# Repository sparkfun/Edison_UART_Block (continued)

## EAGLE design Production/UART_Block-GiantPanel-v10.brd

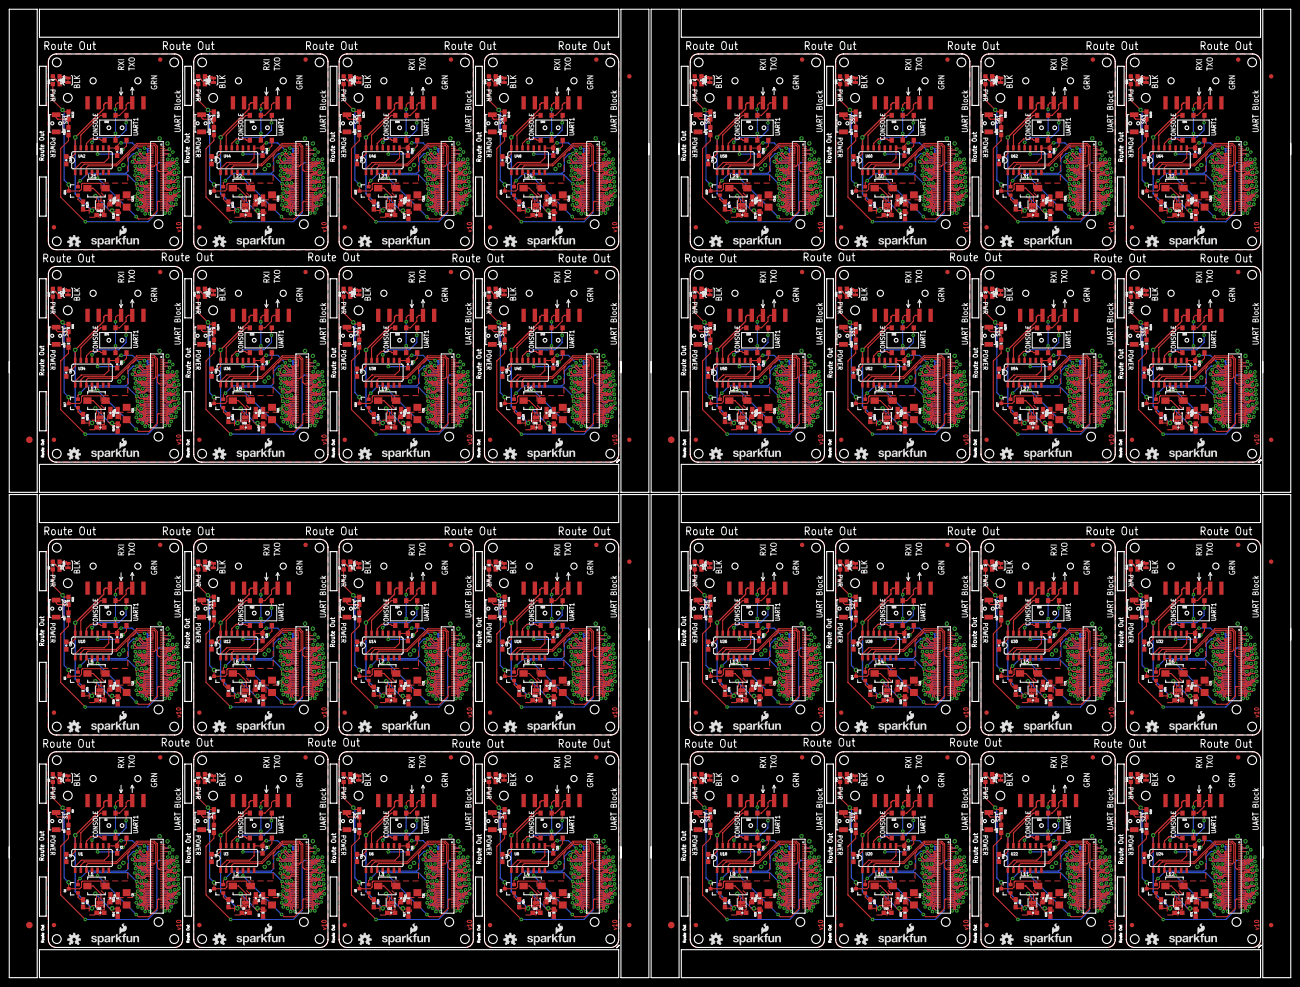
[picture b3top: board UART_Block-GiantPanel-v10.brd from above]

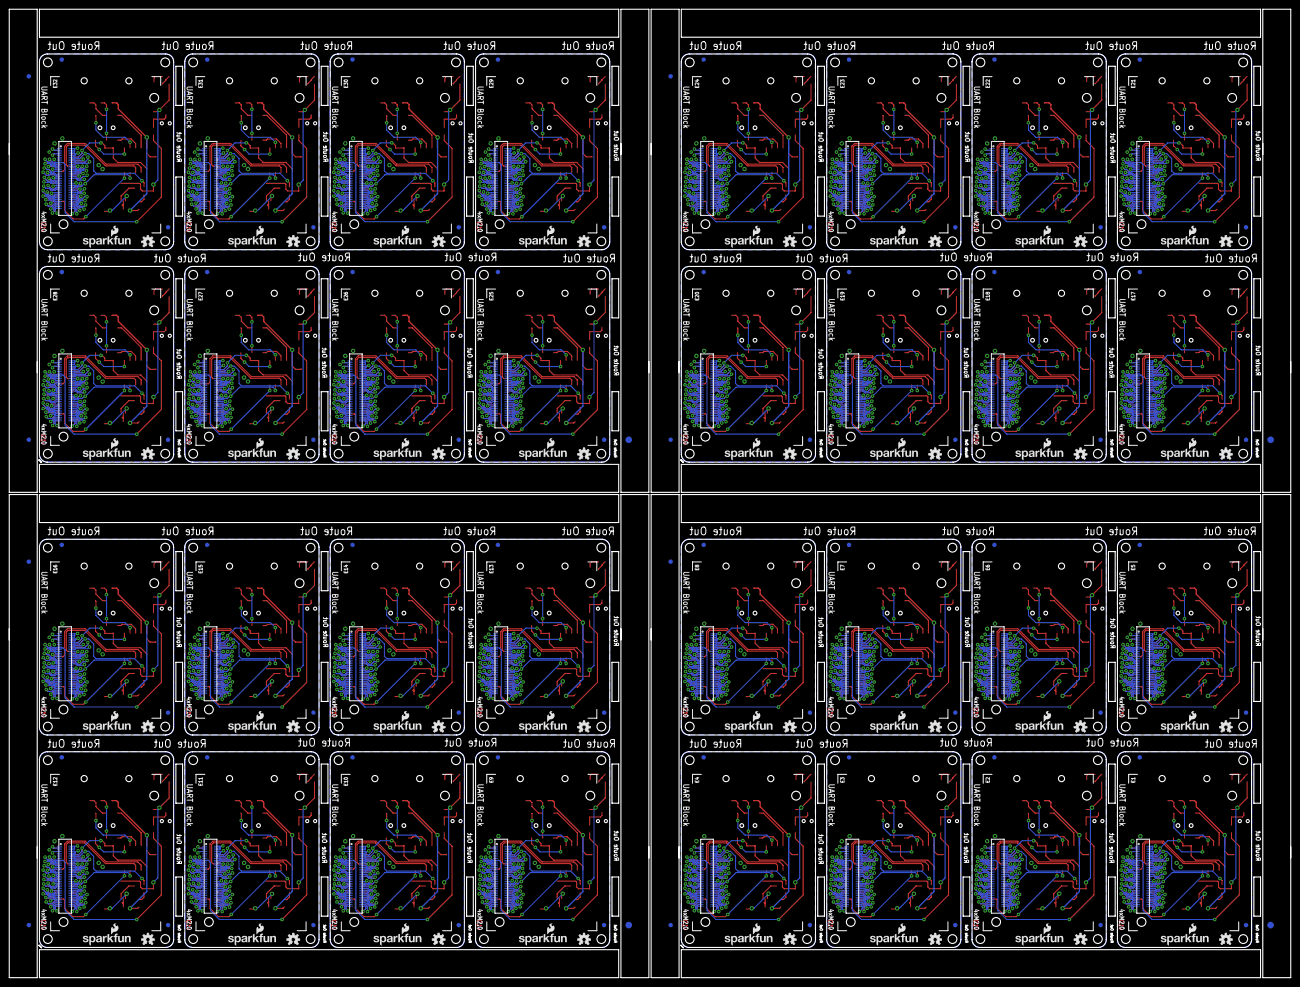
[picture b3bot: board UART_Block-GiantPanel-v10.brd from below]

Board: 2 copper layers, 291.1 x 220.0 mm, 984 parts (204 on the bottom side), 2272 nets.

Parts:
C1, C2, C6, C7, C14, C15, C19, C20, C24, C25, C29, C30, C34, C35, C39, C40, C44, C45, C49, C50, C54, C55, C59, C60, C64, C65, C69, C70, C74, C75, C79, C80, C84, C85, C89, C90, C94, C95, C99, C100, C104, C105, C109, C110, C114, C115, C119, C120, C124, C125, C129, C130, C134, C135, C139, C140, C144, C145, C149, C150, C154, C155, C159, C160: 0.1uF; 0603-CAP
C3, C8, C11, C16, C21, C26, C31, C36, C41, C46, C51, C56, C61, C66, C71, C76, C81, C86, C91, C96, C101, C106, C111, C116, C121, C126, C131, C136, C141, C146, C151, C156: 10uF; 1206
C4, C9, C12, C17, C22, C27, C32, C37, C42, C47, C52, C57, C62, C67, C72, C77, C82, C87, C92, C97, C102, C107, C112, C117, C122, C127, C132, C137, C142, C147, C152, C157: 47pF; 0603-CAP
C5, C10, C13, C18, C23, C28, C33, C38, C43, C48, C53, C58, C63, C68, C73, C78, C83, C88, C93, C98, C103, C108, C113, C118, C123, C128, C133, C138, C143, C148, C153, C158: 4.7uF; 0603-CAP
D1, D2, D3, D4, D5, D6, D7, D8, D9, D10, D11, D12, D13, D14, D15, D16, D17, D18, D19, D20, D21, D22, D23, D24, D25, D26, D27, D28, D29, D30, D31, D32: BLUE; LED-0603
E1, E2, E3, E4, E5, E6, E7, E8, E9, E10, E11, E12, E13, E14, E15, E16, E17, E18, E19, E20, E21, E22, E23, E24, E25, E26, E27, E28, E29, E30, E31, E32: EDISON_CONNECTOR_FULLMOUNTING_HOLES; EDISON_DAUGHTER
E$1, E$2, E$9, E$10, E$15, E$16, E$21, E$22: FIDUCIAL-1.5X3
E$3, E$4, E$5, E$6, E$7, E$8, E$11, E$12, E$13, E$14, E$17, E$18, E$19, E$20, E$23, E$24: FIDUCIAL-1X2
FID1, FID2, FID3, FID4, FID5, FID6, FID7, FID8, FID9, FID10, FID11, FID12, FID13, FID14, FID15, FID16, FID17, FID18, FID19, FID20, FID21, FID22, FID23, FID24, FID25, FID26, FID27, FID28, FID29, FID30, FID31, FID32, FID33, FID34, FID35, FID36, FID37, FID38, FID39, FID40, FID41, FID42, FID43, FID44, FID45, FID46, FID47, FID48, FID49, FID50, FID51, FID52, FID53, FID54, FID55, FID56, FID57, FID58, FID59, FID60, FID61, FID62, FID63, FID64, FID65, FID66, FID67, FID68, FID69, FID70, FID71, FID72, FID73, FID74, FID75, FID76, FID77, FID78, FID79, FID80, FID81, FID82, FID83, FID84, FID85, FID86, FID87, FID88, FID89, FID90, FID91, FID92, FID93, FID94, FID95, FID96, FID97, FID98, FID99, FID100, FID101, FID102, FID103, FID104, FID105, FID106, FID107, FID108, FID109, FID110, FID111, FID112, FID113, FID114, FID115, FID116, FID117, FID118, FID119, FID120, FID121, FID122, FID123, FID124, FID125, FID126, FID127, FID128: FIDUCIAL1X2; FIDUCIAL-1X2
JP1, JP2, JP3, JP4, JP5, JP6, JP7, JP8, JP9, JP10, JP11, JP12, JP13, JP14, JP15, JP16, JP17, JP18, JP19, JP20, JP21, JP22, JP23, JP24, JP25, JP26, JP27, JP28, JP29, JP30, JP31, JP32: 1X06-SMD
L1, L2, L3, L4, L5, L6, L7, L8, L9, L10, L11, L12, L13, L14, L15, L16, L17, L18, L19, L20, L21, L22, L23, L24, L25, L26, L27, L28, L29, L30, L31, L32: INDUCTOR-SRP4020
LOGO1, LOGO3, LOGO6, LOGO7, LOGO10, LOGO11, LOGO14, LOGO15, LOGO18, LOGO19, LOGO22, LOGO23, LOGO26, LOGO27, LOGO30, LOGO31, LOGO34, LOGO35, LOGO38, LOGO39, LOGO42, LOGO43, LOGO46, LOGO47, LOGO50, LOGO51, LOGO54, LOGO55, LOGO58, LOGO59, LOGO62, LOGO63, LOGO66, LOGO67, LOGO70, LOGO71, LOGO74, LOGO75, LOGO78, LOGO79, LOGO82, LOGO83, LOGO86, LOGO87, LOGO90, LOGO91, LOGO94, LOGO95, LOGO98, LOGO99, LOGO102, LOGO103, LOGO106, LOGO107, LOGO110, LOGO111, LOGO114, LOGO115, LOGO118, LOGO119, LOGO122, LOGO123, LOGO126, LOGO127: SFE_LOGO_NAME_FLAME.1_INCH; SFE_LOGO_NAME_FLAME_.1
LOGO2, LOGO4, LOGO5, LOGO8, LOGO9, LOGO12, LOGO13, LOGO16, LOGO17, LOGO20, LOGO21, LOGO24, LOGO25, LOGO28, LOGO29, LOGO32, LOGO33, LOGO36, LOGO37, LOGO40, LOGO41, LOGO44, LOGO45, LOGO48, LOGO49, LOGO52, LOGO53, LOGO56, LOGO57, LOGO60, LOGO61, LOGO64, LOGO65, LOGO68, LOGO69, LOGO72, LOGO73, LOGO76, LOGO77, LOGO80, LOGO81, LOGO84, LOGO85, LOGO88, LOGO89, LOGO92, LOGO93, LOGO96, LOGO97, LOGO100, LOGO101, LOGO104, LOGO105, LOGO108, LOGO109, LOGO112, LOGO113, LOGO116, LOGO117, LOGO120, LOGO121, LOGO124, LOGO125, LOGO128: OSHW-LOGOS; OSHW-LOGO-S
Q1, Q2, Q3, Q4, Q5, Q6, Q7, Q8, Q9, Q10, Q11, Q12, Q13, Q14, Q15, Q16, Q17, Q18, Q19, Q20, Q21, Q22, Q23, Q24, Q25, Q26, Q27, Q28, Q29, Q30, Q31, Q32: BSS138; SOT23-3
R1, R5, R7, R10, R15, R18, R19, R24, R25, R30, R31, R36, R37, R42, R43, R48, R49, R54, R55, R60, R61, R66, R67, R72, R73, R78, R79, R84, R85, R90, R91, R96, R97, R102, R103, R108, R109, R114, R115, R120, R121, R126, R127, R132, R133, R138, R139, R144, R145, R150, R151, R156, R157, R162, R163, R168, R169, R174, R175, R180, R181, R186, R187, R192: 1K; 0603-RES
R2, R8, R11, R20, R26, R32, R38, R44, R50, R56, R62, R68, R74, R80, R86, R92, R98, R104, R110, R116, R122, R128, R134, R140, R146, R152, R158, R164, R170, R176, R182, R188: 10K; 0603-RES
R3, R9, R12, R21, R27, R33, R39, R45, R51, R57, R63, R69, R75, R81, R87, R93, R99, R105, R111, R117, R123, R129, R135, R141, R147, R153, R159, R165, R171, R177, R183, R189: 22; 0603-RES
R4, R13, R16, R22, R28, R34, R40, R46, R52, R58, R64, R70, R76, R82, R88, R94, R100, R106, R112, R118, R124, R130, R136, R142, R148, R154, R160, R166, R172, R178, R184, R190: 680k; 0603-RES
R6, R14, R17, R23, R29, R35, R41, R47, R53, R59, R65, R71, R77, R83, R89, R95, R101, R107, R113, R119, R125, R131, R137, R143, R149, R155, R161, R167, R173, R179, R185, R191: 120k; 0603-RES
S1, S3, S5, S7, S9, S11, S13, S15, S17, S19, S21, S23, S25, S27, S29, S31, S33, S35, S37, S39, S41, S43, S45, S47, S49, S51, S53, S55, S57, S59, S61, S63: POWER; TACTILE_SWITCH-SMD-RIGHT-ANGLE
S2, S4, S6, S8, S10, S12, S14, S16, S18, S20, S22, S24, S26, S28, S30, S32, S34, S36, S38, S40, S42, S44, S46, S48, S50, S52, S54, S56, S58, S60, S62, S64: DPDT; AYZ0202
SJ1, SJ2, SJ3, SJ4, SJ5, SJ6, SJ7, SJ8, SJ9, SJ10, SJ11, SJ12, SJ13, SJ14, SJ15, SJ16, SJ17, SJ18, SJ19, SJ20, SJ21, SJ22, SJ23, SJ24, SJ25, SJ26, SJ27, SJ28, SJ29, SJ30, SJ31, SJ32: JUMPER-PAD-2-NC_BY_TRACE; PAD-JUMPER-2-NC_BY_TRACE_YES_SILK
U1, U3, U6, U8, U10, U12, U14, U16, U18, U20, U22, U24, U26, U28, U30, U32, U34, U36, U38, U40, U42, U44, U46, U48, U50, U52, U54, U56, U58, U60, U62, U64: SO14
U2, U4, U5, U7, U9, U11, U13, U15, U17, U19, U21, U23, U25, U27, U29, U31, U33, U35, U37, U39, U41, U43, U45, U47, U49, U51, U53, U55, U57, U59, U61, U63: TPS62065; WSON-8-PAD
U$1, U$2, U$3, U$4, U$5, U$6, U$7, U$8, U$9, U$10, U$11, U$12, U$13, U$14, U$15, U$16, U$17, U$18, U$19, U$20, U$21, U$22, U$23, U$24, U$25, U$26, U$27, U$28, U$29, U$30, U$31, U$32: EDISON_CONNECTOR_FULLHEADER; DF40C-70DP-0.4(51)

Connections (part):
1.8V: C2.1, E1.12, U1.1, U1.8, U$3.12
1.8V1: C7.1, E2.12, U3.1, U3.8, U$1.12
1.8V2: C15.1, E3.12, U6.1, U6.8, U$2.12
1.8V3: C20.1, E4.12, U8.1, U8.8, U$4.12
1.8V4: C25.1, E5.12, U10.1, U10.8, U$5.12
1.8V5: C30.1, E6.12, U12.1, U12.8, U$6.12
1.8V6: C35.1, E7.12, U14.1, U14.8, U$7.12
1.8V7: C40.1, E8.12, U16.1, U16.8, U$8.12
1.8V8: C45.1, E9.12, U18.1, U18.8, U$9.12
1.8V9: C50.1, E10.12, U20.1, U20.8, U$10.12
1.8V10: C55.1, E11.12, U22.1, U22.8, U$11.12
1.8V11: C60.1, E12.12, U24.1, U24.8, U$12.12
1.8V12: C65.1, E13.12, U26.1, U26.8, U$13.12
1.8V13: C70.1, E14.12, U28.1, U28.8, U$14.12
1.8V14: C75.1, E15.12, U30.1, U30.8, U$15.12
1.8V15: C80.1, E16.12, U32.1, U32.8, U$16.12
1.8V16: C85.1, E17.12, U34.1, U34.8, U$17.12
1.8V17: C90.1, E18.12, U36.1, U36.8, U$18.12
1.8V18: C95.1, E19.12, U38.1, U38.8, U$19.12
1.8V19: C100.1, E20.12, U40.1, U40.8, U$20.12
1.8V20: C105.1, E21.12, U42.1, U42.8, U$21.12
1.8V21: C110.1, E22.12, U44.1, U44.8, U$22.12
1.8V22: C115.1, E23.12, U46.1, U46.8, U$23.12
1.8V23: C120.1, E24.12, U48.1, U48.8, U$24.12
1.8V24: C125.1, E25.12, U50.1, U50.8, U$25.12
1.8V25: C130.1, E26.12, U52.1, U52.8, U$26.12
1.8V26: C135.1, E27.12, U54.1, U54.8, U$27.12
1.8V27: C140.1, E28.12, U56.1, U56.8, U$28.12
1.8V28: C145.1, E29.12, U58.1, U58.8, U$29.12
1.8V29: C150.1, E30.12, U60.1, U60.8, U$30.12
1.8V30: C155.1, E31.12, U62.1, U62.8, U$31.12
1.8V31: C160.1, E32.12, U64.1, U64.8, U$32.12
3.3V: E1.8, E1.10, U$3.8, U$3.10
3.3V1: E2.8, E2.10, U$1.8, U$1.10
3.3V2: E3.8, E3.10, U$2.8, U$2.10
3.3V3: E4.8, E4.10, U$4.8, U$4.10
3.3V4: E5.8, E5.10, U$5.8, U$5.10
3.3V5: E6.8, E6.10, U$6.8, U$6.10
3.3V6: E7.8, E7.10, U$7.8, U$7.10
3.3V7: E8.8, E8.10, U$8.8, U$8.10
3.3V8: E9.8, E9.10, U$9.8, U$9.10
3.3V9: E10.8, E10.10, U$10.8, U$10.10
3.3V10: E11.8, E11.10, U$11.8, U$11.10
3.3V11: E12.8, E12.10, U$12.8, U$12.10
3.3V12: E13.8, E13.10, U$13.8, U$13.10
3.3V13: E14.8, E14.10, U$14.8, U$14.10
3.3V14: E15.8, E15.10, U$15.8, U$15.10
3.3V15: E16.8, E16.10, U$16.8, U$16.10
3.3V16: E17.8, E17.10, U$17.8, U$17.10
3.3V17: E18.8, E18.10, U$18.8, U$18.10
3.3V18: E19.8, E19.10, U$19.8, U$19.10
3.3V19: E20.8, E20.10, U$20.8, U$20.10
3.3V20: E21.8, E21.10, U$21.8, U$21.10
3.3V21: E22.8, E22.10, U$22.8, U$22.10
3.3V22: E23.8, E23.10, U$23.8, U$23.10
3.3V23: E24.8, E24.10, U$24.8, U$24.10
3.3V24: E25.8, E25.10, U$25.8, U$25.10
3.3V25: E26.8, E26.10, U$26.8, U$26.10
3.3V26: E27.8, E27.10, U$27.8, U$27.10
3.3V27: E28.8, E28.10, U$28.8, U$28.10
3.3V28: E29.8, E29.10, U$29.8, U$29.10
3.3V29: E30.8, E30.10, U$30.8, U$30.10
3.3V30: E31.8, E31.10, U$31.8, U$31.10
3.3V31: E32.8, E32.10, U$32.8, U$32.10
DCIN: E1.14, Q1.2, U$3.14
DCIN1: E2.14, Q2.2, U$1.14
DCIN2: E3.14, Q3.2, U$2.14
DCIN3: E4.14, Q4.2, U$4.14
DCIN4: E5.14, Q5.2, U$5.14
DCIN5: E6.14, Q6.2, U$6.14
DCIN6: E7.14, Q7.2, U$7.14
DCIN7: E8.14, Q8.2, U$8.14
DCIN8: E9.14, Q9.2, U$9.14
DCIN9: E10.14, Q10.2, U$10.14
DCIN10: E11.14, Q11.2, U$11.14
DCIN11: E12.14, Q12.2, U$12.14
DCIN12: E13.14, Q13.2, U$13.14
DCIN13: E14.14, Q14.2, U$14.14
DCIN14: E15.14, Q15.2, U$15.14
DCIN15: E16.14, Q16.2, U$16.14
DCIN16: E17.14, Q17.2, U$17.14
DCIN17: E18.14, Q18.2, U$18.14
DCIN18: E19.14, Q19.2, U$19.14
DCIN19: E20.14, Q20.2, U$20.14
DCIN20: E21.14, Q21.2, U$21.14
DCIN21: E22.14, Q22.2, U$22.14
DCIN22: E23.14, Q23.2, U$23.14
DCIN23: E24.14, Q24.2, U$24.14
DCIN24: E25.14, Q25.2, U$25.14
DCIN25: E26.14, Q26.2, U$26.14
DCIN26: E27.14, Q27.2, U$27.14
DCIN27: E28.14, Q28.2, U$28.14
DCIN28: E29.14, Q29.2, U$29.14
DCIN29: E30.14, Q30.2, U$30.14
DCIN30: E31.14, Q31.2, U$31.14
DCIN31: E32.14, Q32.2, U$32.14
FAULT: E1.19, U$3.19
FAULT1: E2.19, U$1.19
FAULT2: E3.19, U$2.19
FAULT3: E4.19, U$4.19
FAULT4: E5.19, U$5.19
FAULT5: E6.19, U$6.19
FAULT6: E7.19, U$7.19
FAULT7: E8.19, U$8.19
FAULT8: E9.19, U$9.19
FAULT9: E10.19, U$10.19
FAULT10: E11.19, U$11.19
FAULT11: E12.19, U$12.19
FAULT12: E13.19, U$13.19
FAULT13: E14.19, U$14.19
FAULT14: E15.19, U$15.19
FAULT15: E16.19, U$16.19
FAULT16: E17.19, U$17.19
FAULT17: E18.19, U$18.19
FAULT18: E19.19, U$19.19
FAULT19: E20.19, U$20.19
FAULT20: E21.19, U$21.19
FAULT21: E22.19, U$22.19
FAULT22: E23.19, U$23.19
FAULT23: E24.19, U$24.19
FAULT24: E25.19, U$25.19
FAULT25: E26.19, U$26.19
FAULT26: E27.19, U$27.19
FAULT27: E28.19, U$28.19
FAULT28: E29.19, U$29.19
FAULT29: E30.19, U$30.19
FAULT30: E31.19, U$31.19
FAULT31: E32.19, U$32.19
FW_RCVR: E1.69, U$3.69
FW_RCVR1: E2.69, U$1.69
FW_RCVR2: E3.69, U$2.69
FW_RCVR3: E4.69, U$4.69
FW_RCVR4: E5.69, U$5.69
FW_RCVR5: E6.69, U$6.69
FW_RCVR6: E7.69, U$7.69
FW_RCVR7: E8.69, U$8.69
FW_RCVR8: E9.69, U$9.69
FW_RCVR9: E10.69, U$10.69
FW_RCVR10: E11.69, U$11.69
FW_RCVR11: E12.69, U$12.69
FW_RCVR12: E13.69, U$13.69
FW_RCVR13: E14.69, U$14.69
FW_RCVR14: E15.69, U$15.69
FW_RCVR15: E16.69, U$16.69
FW_RCVR16: E17.69, U$17.69
FW_RCVR17: E18.69, U$18.69
FW_RCVR18: E19.69, U$19.69
FW_RCVR19: E20.69, U$20.69
FW_RCVR20: E21.69, U$21.69
FW_RCVR21: E22.69, U$22.69
FW_RCVR22: E23.69, U$23.69
FW_RCVR23: E24.69, U$24.69
FW_RCVR24: E25.69, U$25.69
FW_RCVR25: E26.69, U$26.69
FW_RCVR26: E27.69, U$27.69
FW_RCVR27: E28.69, U$28.69
FW_RCVR28: E29.69, U$29.69
FW_RCVR29: E30.69, U$30.69
FW_RCVR30: E31.69, U$31.69
FW_RCVR31: E32.69, U$32.69
GND: C1.2, C2.2, C8.2, C10.2, E1.1, E1.5, E1.9, E1.11, E1.13, E1.15, JP2.5, JP2.6, R14.1, S1.2, SJ3.1, U1.7, U4.1, U4.3, U4.6, U4.PAD, U$3.1, U$3.5, U$3.9, U$3.11, U$3.13, U$3.15
GND1: C3.2, C5.2, C6.2, C7.2, E2.1, E2.5, E2.9, E2.11, E2.13, E2.15, JP1.5, JP1.6, R6.1, S3.2, SJ1.1, U2.1, U2.3, U2.6, U2.PAD, U3.7, U$1.1, U$1.5, U$1.9, U$1.11, U$1.13, U$1.15
GND2: C11.2, C13.2, C14.2, C15.2, E3.1, E3.5, E3.9, E3.11, E3.13, E3.15, JP3.5, JP3.6, R17.1, S5.2, SJ2.1, U5.1, U5.3, U5.6, U5.PAD, U6.7, U$2.1, U$2.5, U$2.9, U$2.11, U$2.13, U$2.15
GND3: C16.2, C18.2, C19.2, C20.2, E4.1, E4.5, E4.9, E4.11, E4.13, E4.15, JP4.5, JP4.6, R23.1, S7.2, SJ4.1, U7.1, U7.3, U7.6, U7.PAD, U8.7, U$4.1, U$4.5, U$4.9, U$4.11, U$4.13, U$4.15
GND4: C21.2, C23.2, C24.2, C25.2, E5.1, E5.5, E5.9, E5.11, E5.13, E5.15, JP5.5, JP5.6, R29.1, S9.2, SJ5.1, U9.1, U9.3, U9.6, U9.PAD, U10.7, U$5.1, U$5.5, U$5.9, U$5.11, U$5.13, U$5.15
GND5: C26.2, C28.2, C29.2, C30.2, E6.1, E6.5, E6.9, E6.11, E6.13, E6.15, JP6.5, JP6.6, R35.1, S11.2, SJ6.1, U11.1, U11.3, U11.6, U11.PAD, U12.7, U$6.1, U$6.5, U$6.9, U$6.11, U$6.13, U$6.15
GND6: C31.2, C33.2, C34.2, C35.2, E7.1, E7.5, E7.9, E7.11, E7.13, E7.15, JP7.5, JP7.6, R41.1, S13.2, SJ7.1, U13.1, U13.3, U13.6, U13.PAD, U14.7, U$7.1, U$7.5, U$7.9, U$7.11, U$7.13, U$7.15
GND7: C36.2, C38.2, C39.2, C40.2, E8.1, E8.5, E8.9, E8.11, E8.13, E8.15, JP8.5, JP8.6, R47.1, S15.2, SJ8.1, U15.1, U15.3, U15.6, U15.PAD, U16.7, U$8.1, U$8.5, U$8.9, U$8.11, U$8.13, U$8.15
GND8: C41.2, C43.2, C44.2, C45.2, E9.1, E9.5, E9.9, E9.11, E9.13, E9.15, JP9.5, JP9.6, R53.1, S17.2, SJ9.1, U17.1, U17.3, U17.6, U17.PAD, U18.7, U$9.1, U$9.5, U$9.9, U$9.11, U$9.13, U$9.15
GND9: C46.2, C48.2, C49.2, C50.2, E10.1, E10.5, E10.9, E10.11, E10.13, E10.15, JP10.5, JP10.6, R59.1, S19.2, SJ10.1, U19.1, U19.3, U19.6, U19.PAD, U20.7, U$10.1, U$10.5, U$10.9, U$10.11, U$10.13, U$10.15
GND10: C51.2, C53.2, C54.2, C55.2, E11.1, E11.5, E11.9, E11.11, E11.13, E11.15, JP11.5, JP11.6, R65.1, S21.2, SJ11.1, U21.1, U21.3, U21.6, U21.PAD, U22.7, U$11.1, U$11.5, U$11.9, U$11.11, U$11.13, U$11.15
GND11: C56.2, C58.2, C59.2, C60.2, E12.1, E12.5, E12.9, E12.11, E12.13, E12.15, JP12.5, JP12.6, R71.1, S23.2, SJ12.1, U23.1, U23.3, U23.6, U23.PAD, U24.7, U$12.1, U$12.5, U$12.9, U$12.11, U$12.13, U$12.15
GND12: C61.2, C63.2, C64.2, C65.2, E13.1, E13.5, E13.9, E13.11, E13.13, E13.15, JP13.5, JP13.6, R77.1, S25.2, SJ13.1, U25.1, U25.3, U25.6, U25.PAD, U26.7, U$13.1, U$13.5, U$13.9, U$13.11, U$13.13, U$13.15
GND13: C66.2, C68.2, C69.2, C70.2, E14.1, E14.5, E14.9, E14.11, E14.13, E14.15, JP14.5, JP14.6, R83.1, S27.2, SJ14.1, U27.1, U27.3, U27.6, U27.PAD, U28.7, U$14.1, U$14.5, U$14.9, U$14.11, U$14.13, U$14.15
GND14: C71.2, C73.2, C74.2, C75.2, E15.1, E15.5, E15.9, E15.11, E15.13, E15.15, JP15.5, JP15.6, R89.1, S29.2, SJ15.1, U29.1, U29.3, U29.6, U29.PAD, U30.7, U$15.1, U$15.5, U$15.9, U$15.11, U$15.13, U$15.15
GND15: C76.2, C78.2, C79.2, C80.2, E16.1, E16.5, E16.9, E16.11, E16.13, E16.15, JP16.5, JP16.6, R95.1, S31.2, SJ16.1, U31.1, U31.3, U31.6, U31.PAD, U32.7, U$16.1, U$16.5, U$16.9, U$16.11, U$16.13, U$16.15
GND16: C81.2, C83.2, C84.2, C85.2, E17.1, E17.5, E17.9, E17.11, E17.13, E17.15, JP17.5, JP17.6, R101.1, S33.2, SJ17.1, U33.1, U33.3, U33.6, U33.PAD, U34.7, U$17.1, U$17.5, U$17.9, U$17.11, U$17.13, U$17.15
GND17: C86.2, C88.2, C89.2, C90.2, E18.1, E18.5, E18.9, E18.11, E18.13, E18.15, JP18.5, JP18.6, R107.1, S35.2, SJ18.1, U35.1, U35.3, U35.6, U35.PAD, U36.7, U$18.1, U$18.5, U$18.9, U$18.11, U$18.13, U$18.15
GND18: C91.2, C93.2, C94.2, C95.2, E19.1, E19.5, E19.9, E19.11, E19.13, E19.15, JP19.5, JP19.6, R113.1, S37.2, SJ19.1, U37.1, U37.3, U37.6, U37.PAD, U38.7, U$19.1, U$19.5, U$19.9, U$19.11, U$19.13, U$19.15
GND19: C96.2, C98.2, C99.2, C100.2, E20.1, E20.5, E20.9, E20.11, E20.13, E20.15, JP20.5, JP20.6, R119.1, S39.2, SJ20.1, U39.1, U39.3, U39.6, U39.PAD, U40.7, U$20.1, U$20.5, U$20.9, U$20.11, U$20.13, U$20.15
GND20: C101.2, C103.2, C104.2, C105.2, E21.1, E21.5, E21.9, E21.11, E21.13, E21.15, JP21.5, JP21.6, R125.1, S41.2, SJ21.1, U41.1, U41.3, U41.6, U41.PAD, U42.7, U$21.1, U$21.5, U$21.9, U$21.11, U$21.13, U$21.15
GND21: C106.2, C108.2, C109.2, C110.2, E22.1, E22.5, E22.9, E22.11, E22.13, E22.15, JP22.5, JP22.6, R131.1, S43.2, SJ22.1, U43.1, U43.3, U43.6, U43.PAD, U44.7, U$22.1, U$22.5, U$22.9, U$22.11, U$22.13, U$22.15
GND22: C111.2, C113.2, C114.2, C115.2, E23.1, E23.5, E23.9, E23.11, E23.13, E23.15, JP23.5, JP23.6, R137.1, S45.2, SJ23.1, U45.1, U45.3, U45.6, U45.PAD, U46.7, U$23.1, U$23.5, U$23.9, U$23.11, U$23.13, U$23.15
GND23: C116.2, C118.2, C119.2, C120.2, E24.1, E24.5, E24.9, E24.11, E24.13, E24.15, JP24.5, JP24.6, R143.1, S47.2, SJ24.1, U47.1, U47.3, U47.6, U47.PAD, U48.7, U$24.1, U$24.5, U$24.9, U$24.11, U$24.13, U$24.15
GND24: C121.2, C123.2, C124.2, C125.2, E25.1, E25.5, E25.9, E25.11, E25.13, E25.15, JP25.5, JP25.6, R149.1, S49.2, SJ25.1, U49.1, U49.3, U49.6, U49.PAD, U50.7, U$25.1, U$25.5, U$25.9, U$25.11, U$25.13, U$25.15
GND25: C126.2, C128.2, C129.2, C130.2, E26.1, E26.5, E26.9, E26.11, E26.13, E26.15, JP26.5, JP26.6, R155.1, S51.2, SJ26.1, U51.1, U51.3, U51.6, U51.PAD, U52.7, U$26.1, U$26.5, U$26.9, U$26.11, U$26.13, U$26.15
GND26: C131.2, C133.2, C134.2, C135.2, E27.1, E27.5, E27.9, E27.11, E27.13, E27.15, JP27.5, JP27.6, R161.1, S53.2, SJ27.1, U53.1, U53.3, U53.6, U53.PAD, U54.7, U$27.1, U$27.5, U$27.9, U$27.11, U$27.13, U$27.15
GND27: C136.2, C138.2, C139.2, C140.2, E28.1, E28.5, E28.9, E28.11, E28.13, E28.15, JP28.5, JP28.6, R167.1, S55.2, SJ28.1, U55.1, U55.3, U55.6, U55.PAD, U56.7, U$28.1, U$28.5, U$28.9, U$28.11, U$28.13, U$28.15
GND28: C141.2, C143.2, C144.2, C145.2, E29.1, E29.5, E29.9, E29.11, E29.13, E29.15, JP29.5, JP29.6, R173.1, S57.2, SJ29.1, U57.1, U57.3, U57.6, U57.PAD, U58.7, U$29.1, U$29.5, U$29.9, U$29.11, U$29.13, U$29.15
GND29: C146.2, C148.2, C149.2, C150.2, E30.1, E30.5, E30.9, E30.11, E30.13, E30.15, JP30.5, JP30.6, R179.1, S59.2, SJ30.1, U59.1, U59.3, U59.6, U59.PAD, U60.7, U$30.1, U$30.5, U$30.9, U$30.11, U$30.13, U$30.15
GND30: C151.2, C153.2, C154.2, C155.2, E31.1, E31.5, E31.9, E31.11, E31.13, E31.15, JP31.5, JP31.6, R185.1, S61.2, SJ31.1, U61.1, U61.3, U61.6, U61.PAD, U62.7, U$31.1, U$31.5, U$31.9, U$31.11, U$31.13, U$31.15
GND31: C156.2, C158.2, C159.2, C160.2, E32.1, E32.5, E32.9, E32.11, E32.13, E32.15, JP32.5, JP32.6, R191.1, S63.2, SJ32.1, U63.1, U63.3, U63.6, U63.PAD, U64.7, U$32.1, U$32.5, U$32.9, U$32.11, U$32.13, U$32.15
GP1: E2.48, U$1.48
GP2: E2.42, U$1.42
GP3: E2.34, U$1.34
GP4: E2.32, U$1.32
GP5: E2.30, U$1.30
GP6: E2.28, U$1.28
GP7: E2.26, U$1.26
GP8: E2.25, U$1.25
GP9: E2.24, U$1.24
GP10: E3.48, U$2.48
GP11: E3.42, U$2.42
GP12: E3.34, U$2.34
GP12_PWM0: E1.35, U$3.35
GP12_PWM1: E2.35, U$1.35
GP12_PWM2: E3.35, U$2.35
GP12_PWM3: E4.35, U$4.35
GP12_PWM4: E5.35, U$5.35
GP12_PWM5: E6.35, U$6.35
GP12_PWM6: E7.35, U$7.35
GP12_PWM7: E8.35, U$8.35
GP12_PWM8: E9.35, U$9.35
GP12_PWM9: E10.35, U$10.35
GP12_PWM10: E11.35, U$11.35
GP12_PWM11: E12.35, U$12.35
GP12_PWM12: E13.35, U$13.35
GP12_PWM13: E14.35, U$14.35
GP12_PWM14: E15.35, U$15.35
GP12_PWM15: E16.35, U$16.35
GP12_PWM16: E17.35, U$17.35
GP12_PWM17: E18.35, U$18.35
GP12_PWM18: E19.35, U$19.35
GP12_PWM19: E20.35, U$20.35
GP12_PWM20: E21.35, U$21.35
GP12_PWM21: E22.35, U$22.35
GP12_PWM22: E23.35, U$23.35
GP12_PWM23: E24.35, U$24.35
GP12_PWM24: E25.35, U$25.35
GP12_PWM25: E26.35, U$26.35
GP12_PWM26: E27.35, U$27.35
GP12_PWM27: E28.35, U$28.35
GP12_PWM28: E29.35, U$29.35
GP12_PWM29: E30.35, U$30.35
GP12_PWM30: E31.35, U$31.35
GP12_PWM31: E32.35, U$32.35
GP13: E3.32, U$2.32
GP13_PWM1: E1.33, U$3.33
GP13_PWM2: E2.33, U$1.33
GP13_PWM3: E3.33, U$2.33
GP13_PWM4: E4.33, U$4.33
GP13_PWM5: E5.33, U$5.33
GP13_PWM6: E6.33, U$6.33
GP13_PWM7: E7.33, U$7.33
GP13_PWM8: E8.33, U$8.33
GP13_PWM9: E9.33, U$9.33
GP13_PWM10: E10.33, U$10.33
GP13_PWM11: E11.33, U$11.33
GP13_PWM12: E12.33, U$12.33
GP13_PWM13: E13.33, U$13.33
GP13_PWM14: E14.33, U$14.33
GP13_PWM15: E15.33, U$15.33
GP13_PWM16: E16.33, U$16.33
GP13_PWM17: E17.33, U$17.33
GP13_PWM18: E18.33, U$18.33
GP13_PWM19: E19.33, U$19.33
GP13_PWM20: E20.33, U$20.33
GP13_PWM21: E21.33, U$21.33
GP13_PWM22: E22.33, U$22.33
GP13_PWM23: E23.33, U$23.33
GP13_PWM24: E24.33, U$24.33
GP13_PWM25: E25.33, U$25.33
GP13_PWM26: E26.33, U$26.33
GP13_PWM27: E27.33, U$27.33
GP13_PWM28: E28.33, U$28.33
GP13_PWM29: E29.33, U$29.33
GP13_PWM30: E30.33, U$30.33
GP13_PWM31: E31.33, U$31.33
GP13_PWM32: E32.33, U$32.33
GP14: E1.48, U$3.48
GP15: E1.42, U$3.42
GP16: E3.30, U$2.30
GP17: E3.28, U$2.28
GP18: E3.26, U$2.26
GP19: E3.25, U$2.25
GP19_I2C_1_SCL: E1.41, U$3.41
GP19_I2C_1_SCL1: E2.41, U$1.41
GP19_I2C_1_SCL2: E3.41, U$2.41
GP19_I2C_1_SCL3: E4.41, U$4.41
GP19_I2C_1_SCL4: E5.41, U$5.41
GP19_I2C_1_SCL5: E6.41, U$6.41
GP19_I2C_1_SCL6: E7.41, U$7.41
GP19_I2C_1_SCL7: E8.41, U$8.41
GP19_I2C_1_SCL8: E9.41, U$9.41
GP19_I2C_1_SCL9: E10.41, U$10.41
GP19_I2C_1_SCL10: E11.41, U$11.41
GP19_I2C_1_SCL11: E12.41, U$12.41
GP19_I2C_1_SCL12: E13.41, U$13.41
GP19_I2C_1_SCL13: E14.41, U$14.41
GP19_I2C_1_SCL14: E15.41, U$15.41
GP19_I2C_1_SCL15: E16.41, U$16.41
GP19_I2C_1_SCL16: E17.41, U$17.41
GP19_I2C_1_SCL17: E18.41, U$18.41
GP19_I2C_1_SCL18: E19.41, U$19.41
GP19_I2C_1_SCL19: E20.41, U$20.41
GP19_I2C_1_SCL20: E21.41, U$21.41
GP19_I2C_1_SCL21: E22.41, U$22.41
GP19_I2C_1_SCL22: E23.41, U$23.41
GP19_I2C_1_SCL23: E24.41, U$24.41
GP19_I2C_1_SCL24: E25.41, U$25.41
GP19_I2C_1_SCL25: E26.41, U$26.41
GP19_I2C_1_SCL26: E27.41, U$27.41
GP19_I2C_1_SCL27: E28.41, U$28.41
GP19_I2C_1_SCL28: E29.41, U$29.41
GP19_I2C_1_SCL29: E30.41, U$30.41
GP19_I2C_1_SCL30: E31.41, U$31.41
GP19_I2C_1_SCL31: E32.41, U$32.41
GP20: E3.24, U$2.24
GP20_I2C_1_SDA: E1.43, U$3.43
GP20_I2C_1_SDA1: E2.43, U$1.43
GP20_I2C_1_SDA2: E3.43, U$2.43
GP20_I2C_1_SDA3: E4.43, U$4.43
GP20_I2C_1_SDA4: E5.43, U$5.43
GP20_I2C_1_SDA5: E6.43, U$6.43
GP20_I2C_1_SDA6: E7.43, U$7.43
GP20_I2C_1_SDA7: E8.43, U$8.43
GP20_I2C_1_SDA8: E9.43, U$9.43
GP20_I2C_1_SDA9: E10.43, U$10.43
GP20_I2C_1_SDA10: E11.43, U$11.43
GP20_I2C_1_SDA11: E12.43, U$12.43
GP20_I2C_1_SDA12: E13.43, U$13.43
GP20_I2C_1_SDA13: E14.43, U$14.43
GP20_I2C_1_SDA14: E15.43, U$15.43
GP20_I2C_1_SDA15: E16.43, U$16.43
GP20_I2C_1_SDA16: E17.43, U$17.43
GP20_I2C_1_SDA17: E18.43, U$18.43
GP20_I2C_1_SDA18: E19.43, U$19.43
GP20_I2C_1_SDA19: E20.43, U$20.43
GP20_I2C_1_SDA20: E21.43, U$21.43
GP20_I2C_1_SDA21: E22.43, U$22.43
GP20_I2C_1_SDA22: E23.43, U$23.43
GP20_I2C_1_SDA23: E24.43, U$24.43
GP20_I2C_1_SDA24: E25.43, U$25.43
GP20_I2C_1_SDA25: E26.43, U$26.43
GP20_I2C_1_SDA26: E27.43, U$27.43
GP20_I2C_1_SDA27: E28.43, U$28.43
GP20_I2C_1_SDA28: E29.43, U$29.43
GP20_I2C_1_SDA29: E30.43, U$30.43
GP20_I2C_1_SDA30: E31.43, U$31.43
GP20_I2C_1_SDA31: E32.43, U$32.43
GP21: E4.48, U$4.48
GP22: E4.42, U$4.42
GP23: E4.34, U$4.34
GP24: E4.32, U$4.32
GP25: E4.30, U$4.30
GP26: E4.28, U$4.28
GP27: E4.26, U$4.26
GP27_I2C_6_SCL: E1.45, U$3.45
GP27_I2C_6_SCL1: E2.45, U$1.45
GP27_I2C_6_SCL2: E3.45, U$2.45
GP27_I2C_6_SCL3: E4.45, U$4.45
GP27_I2C_6_SCL4: E5.45, U$5.45
GP27_I2C_6_SCL5: E6.45, U$6.45
GP27_I2C_6_SCL6: E7.45, U$7.45
GP27_I2C_6_SCL7: E8.45, U$8.45
GP27_I2C_6_SCL8: E9.45, U$9.45
GP27_I2C_6_SCL9: E10.45, U$10.45
GP27_I2C_6_SCL10: E11.45, U$11.45
GP27_I2C_6_SCL11: E12.45, U$12.45
GP27_I2C_6_SCL12: E13.45, U$13.45
GP27_I2C_6_SCL13: E14.45, U$14.45
GP27_I2C_6_SCL14: E15.45, U$15.45
GP27_I2C_6_SCL15: E16.45, U$16.45
GP27_I2C_6_SCL16: E17.45, U$17.45
GP27_I2C_6_SCL17: E18.45, U$18.45
GP27_I2C_6_SCL18: E19.45, U$19.45
GP27_I2C_6_SCL19: E20.45, U$20.45
GP27_I2C_6_SCL20: E21.45, U$21.45
GP27_I2C_6_SCL21: E22.45, U$22.45
GP27_I2C_6_SCL22: E23.45, U$23.45
GP27_I2C_6_SCL23: E24.45, U$24.45
GP27_I2C_6_SCL24: E25.45, U$25.45
GP27_I2C_6_SCL25: E26.45, U$26.45
GP27_I2C_6_SCL26: E27.45, U$27.45
GP27_I2C_6_SCL27: E28.45, U$28.45
GP27_I2C_6_SCL28: E29.45, U$29.45
GP27_I2C_6_SCL29: E30.45, U$30.45
GP27_I2C_6_SCL30: E31.45, U$31.45
GP27_I2C_6_SCL31: E32.45, U$32.45
GP28: E4.25, U$4.25
GP28_I2C_6_SDA: E1.47, U$3.47
GP28_I2C_6_SDA1: E2.47, U$1.47
GP28_I2C_6_SDA2: E3.47, U$2.47
GP28_I2C_6_SDA3: E4.47, U$4.47
GP28_I2C_6_SDA4: E5.47, U$5.47
GP28_I2C_6_SDA5: E6.47, U$6.47
GP28_I2C_6_SDA6: E7.47, U$7.47
GP28_I2C_6_SDA7: E8.47, U$8.47
GP28_I2C_6_SDA8: E9.47, U$9.47
GP28_I2C_6_SDA9: E10.47, U$10.47
GP28_I2C_6_SDA10: E11.47, U$11.47
GP28_I2C_6_SDA11: E12.47, U$12.47
GP28_I2C_6_SDA12: E13.47, U$13.47
GP28_I2C_6_SDA13: E14.47, U$14.47
GP28_I2C_6_SDA14: E15.47, U$15.47
GP28_I2C_6_SDA15: E16.47, U$16.47
GP28_I2C_6_SDA16: E17.47, U$17.47
GP28_I2C_6_SDA17: E18.47, U$18.47
GP28_I2C_6_SDA18: E19.47, U$19.47
GP28_I2C_6_SDA19: E20.47, U$20.47
GP28_I2C_6_SDA20: E21.47, U$21.47
GP28_I2C_6_SDA21: E22.47, U$22.47
GP28_I2C_6_SDA22: E23.47, U$23.47
GP28_I2C_6_SDA23: E24.47, U$24.47
GP28_I2C_6_SDA24: E25.47, U$25.47
GP28_I2C_6_SDA25: E26.47, U$26.47
GP28_I2C_6_SDA26: E27.47, U$27.47
GP28_I2C_6_SDA27: E28.47, U$28.47
GP28_I2C_6_SDA28: E29.47, U$29.47
GP28_I2C_6_SDA29: E30.47, U$30.47
GP28_I2C_6_SDA30: E31.47, U$31.47
GP28_I2C_6_SDA31: E32.47, U$32.47
GP29: E4.24, U$4.24
GP30: E5.48, U$5.48
GP31: E5.42, U$5.42
GP32: E5.34, U$5.34
GP33: E5.32, U$5.32
GP34: E5.30, U$5.30
GP35: E5.28, U$5.28
GP36: E5.26, U$5.26
GP37: E5.25, U$5.25
GP38: E5.24, U$5.24
GP39: E6.48, U$6.48
GP40: E6.42, U$6.42
GP40_I2S_2_CLK: E1.52, U$3.52
GP40_I2S_2_CLK1: E2.52, U$1.52
GP40_I2S_2_CLK2: E3.52, U$2.52
GP40_I2S_2_CLK3: E4.52, U$4.52
GP40_I2S_2_CLK4: E5.52, U$5.52
GP40_I2S_2_CLK5: E6.52, U$6.52
GP40_I2S_2_CLK6: E7.52, U$7.52
GP40_I2S_2_CLK7: E8.52, U$8.52
GP40_I2S_2_CLK8: E9.52, U$9.52
GP40_I2S_2_CLK9: E10.52, U$10.52
GP40_I2S_2_CLK10: E11.52, U$11.52
GP40_I2S_2_CLK11: E12.52, U$12.52
GP40_I2S_2_CLK12: E13.52, U$13.52
GP40_I2S_2_CLK13: E14.52, U$14.52
GP40_I2S_2_CLK14: E15.52, U$15.52
GP40_I2S_2_CLK15: E16.52, U$16.52
GP40_I2S_2_CLK16: E17.52, U$17.52
GP40_I2S_2_CLK17: E18.52, U$18.52
GP40_I2S_2_CLK18: E19.52, U$19.52
GP40_I2S_2_CLK19: E20.52, U$20.52
GP40_I2S_2_CLK20: E21.52, U$21.52
GP40_I2S_2_CLK21: E22.52, U$22.52
GP40_I2S_2_CLK22: E23.52, U$23.52
GP40_I2S_2_CLK23: E24.52, U$24.52
GP40_I2S_2_CLK24: E25.52, U$25.52
GP40_I2S_2_CLK25: E26.52, U$26.52
GP40_I2S_2_CLK26: E27.52, U$27.52
GP40_I2S_2_CLK27: E28.52, U$28.52
GP40_I2S_2_CLK28: E29.52, U$29.52
GP40_I2S_2_CLK29: E30.52, U$30.52
GP40_I2S_2_CLK30: E31.52, U$31.52
GP40_I2S_2_CLK31: E32.52, U$32.52
GP41: E6.34, U$6.34
GP41_I2S_2_FS: E1.54, U$3.54
GP41_I2S_2_FS1: E2.54, U$1.54
GP41_I2S_2_FS2: E3.54, U$2.54
GP41_I2S_2_FS3: E4.54, U$4.54
GP41_I2S_2_FS4: E5.54, U$5.54
GP41_I2S_2_FS5: E6.54, U$6.54
GP41_I2S_2_FS6: E7.54, U$7.54
GP41_I2S_2_FS7: E8.54, U$8.54
GP41_I2S_2_FS8: E9.54, U$9.54
GP41_I2S_2_FS9: E10.54, U$10.54
GP41_I2S_2_FS10: E11.54, U$11.54
GP41_I2S_2_FS11: E12.54, U$12.54
GP41_I2S_2_FS12: E13.54, U$13.54
GP41_I2S_2_FS13: E14.54, U$14.54
GP41_I2S_2_FS14: E15.54, U$15.54
GP41_I2S_2_FS15: E16.54, U$16.54
GP41_I2S_2_FS16: E17.54, U$17.54
GP41_I2S_2_FS17: E18.54, U$18.54
GP41_I2S_2_FS18: E19.54, U$19.54
GP41_I2S_2_FS19: E20.54, U$20.54
GP41_I2S_2_FS20: E21.54, U$21.54
GP41_I2S_2_FS21: E22.54, U$22.54
GP41_I2S_2_FS22: E23.54, U$23.54
GP41_I2S_2_FS23: E24.54, U$24.54
GP41_I2S_2_FS24: E25.54, U$25.54
GP41_I2S_2_FS25: E26.54, U$26.54
GP41_I2S_2_FS26: E27.54, U$27.54
GP41_I2S_2_FS27: E28.54, U$28.54
GP41_I2S_2_FS28: E29.54, U$29.54
GP41_I2S_2_FS29: E30.54, U$30.54
GP41_I2S_2_FS30: E31.54, U$31.54
GP41_I2S_2_FS31: E32.54, U$32.54
GP42: E6.32, U$6.32
GP42_I2S_2_RXD: E1.50, U$3.50
GP42_I2S_2_RXD1: E2.50, U$1.50
GP42_I2S_2_RXD2: E3.50, U$2.50
GP42_I2S_2_RXD3: E4.50, U$4.50
GP42_I2S_2_RXD4: E5.50, U$5.50
GP42_I2S_2_RXD5: E6.50, U$6.50
GP42_I2S_2_RXD6: E7.50, U$7.50
GP42_I2S_2_RXD7: E8.50, U$8.50
GP42_I2S_2_RXD8: E9.50, U$9.50
GP42_I2S_2_RXD9: E10.50, U$10.50
GP42_I2S_2_RXD10: E11.50, U$11.50
GP42_I2S_2_RXD11: E12.50, U$12.50
GP42_I2S_2_RXD12: E13.50, U$13.50
GP42_I2S_2_RXD13: E14.50, U$14.50
GP42_I2S_2_RXD14: E15.50, U$15.50
GP42_I2S_2_RXD15: E16.50, U$16.50
GP42_I2S_2_RXD16: E17.50, U$17.50
GP42_I2S_2_RXD17: E18.50, U$18.50
GP42_I2S_2_RXD18: E19.50, U$19.50
GP42_I2S_2_RXD19: E20.50, U$20.50
GP42_I2S_2_RXD20: E21.50, U$21.50
GP42_I2S_2_RXD21: E22.50, U$22.50
GP42_I2S_2_RXD22: E23.50, U$23.50
GP42_I2S_2_RXD23: E24.50, U$24.50
GP42_I2S_2_RXD24: E25.50, U$25.50
GP42_I2S_2_RXD25: E26.50, U$26.50
GP42_I2S_2_RXD26: E27.50, U$27.50
GP42_I2S_2_RXD27: E28.50, U$28.50
GP42_I2S_2_RXD28: E29.50, U$29.50
GP42_I2S_2_RXD29: E30.50, U$30.50
GP42_I2S_2_RXD30: E31.50, U$31.50
GP42_I2S_2_RXD31: E32.50, U$32.50
GP43: E6.30, U$6.30
GP43_I2S_2_TXD: E1.56, U$3.56
GP43_I2S_2_TXD1: E2.56, U$1.56
GP43_I2S_2_TXD2: E3.56, U$2.56
GP43_I2S_2_TXD3: E4.56, U$4.56
GP43_I2S_2_TXD4: E5.56, U$5.56
GP43_I2S_2_TXD5: E6.56, U$6.56
GP43_I2S_2_TXD6: E7.56, U$7.56
GP43_I2S_2_TXD7: E8.56, U$8.56
GP43_I2S_2_TXD8: E9.56, U$9.56
GP43_I2S_2_TXD9: E10.56, U$10.56
GP43_I2S_2_TXD10: E11.56, U$11.56
GP43_I2S_2_TXD11: E12.56, U$12.56
GP43_I2S_2_TXD12: E13.56, U$13.56
GP43_I2S_2_TXD13: E14.56, U$14.56
GP43_I2S_2_TXD14: E15.56, U$15.56
GP43_I2S_2_TXD15: E16.56, U$16.56
GP43_I2S_2_TXD16: E17.56, U$17.56
GP43_I2S_2_TXD17: E18.56, U$18.56
GP43_I2S_2_TXD18: E19.56, U$19.56
GP43_I2S_2_TXD19: E20.56, U$20.56
GP43_I2S_2_TXD20: E21.56, U$21.56
GP43_I2S_2_TXD21: E22.56, U$22.56
GP43_I2S_2_TXD22: E23.56, U$23.56
GP43_I2S_2_TXD23: E24.56, U$24.56
GP43_I2S_2_TXD24: E25.56, U$25.56
GP43_I2S_2_TXD25: E26.56, U$26.56
GP43_I2S_2_TXD26: E27.56, U$27.56
GP43_I2S_2_TXD27: E28.56, U$28.56
GP43_I2S_2_TXD28: E29.56, U$29.56
GP43_I2S_2_TXD29: E30.56, U$30.56
GP43_I2S_2_TXD30: E31.56, U$31.56
GP43_I2S_2_TXD31: E32.56, U$32.56
GP44: E1.24, U$3.24
GP45: E1.26, U$3.26
GP46: E1.28, U$3.28
GP47: E1.30, U$3.30
GP48: E1.32, U$3.32
GP49: E1.34, U$3.34
GP50: E6.28, U$6.28
GP51: E6.26, U$6.26
GP52: E6.25, U$6.25
GP53: E6.24, U$6.24
GP54: E7.48, U$7.48
GP55: E7.42, U$7.42
GP56: E7.34, U$7.34
GP57: E7.32, U$7.32
GP58: E7.30, U$7.30
GP59: E7.28, U$7.28
GP60: E7.26, U$7.26
GP61: E7.25, U$7.25
GP62: E7.24, U$7.24
GP63: E8.48, U$8.48
GP64: E8.42, U$8.42
GP65: E8.34, U$8.34
GP66: E8.32, U$8.32
GP67: E8.30, U$8.30
GP68: E8.28, U$8.28
GP69: E8.26, U$8.26
GP70: E8.25, U$8.25
GP71: E8.24, U$8.24
GP72: E9.48, U$9.48
GP73: E9.42, U$9.42
GP74: E9.34, U$9.34
GP75: E9.32, U$9.32
GP76: E9.30, U$9.30
GP77: E9.28, U$9.28
GP77_SD_0_CD#: E1.60, U$3.60
GP77_SD_0_CD#1: E2.60, U$1.60
GP77_SD_0_CD#2: E3.60, U$2.60
GP77_SD_0_CD#3: E4.60, U$4.60
GP77_SD_0_CD#4: E5.60, U$5.60
GP77_SD_0_CD#5: E6.60, U$6.60
GP77_SD_0_CD#6: E7.60, U$7.60
GP77_SD_0_CD#7: E8.60, U$8.60
GP77_SD_0_CD#8: E9.60, U$9.60
GP77_SD_0_CD#9: E10.60, U$10.60
GP77_SD_0_CD#10: E11.60, U$11.60
GP77_SD_0_CD#11: E12.60, U$12.60
GP77_SD_0_CD#12: E13.60, U$13.60
GP77_SD_0_CD#13: E14.60, U$14.60
GP77_SD_0_CD#14: E15.60, U$15.60
GP77_SD_0_CD#15: E16.60, U$16.60
GP77_SD_0_CD#16: E17.60, U$17.60
GP77_SD_0_CD#17: E18.60, U$18.60
GP77_SD_0_CD#18: E19.60, U$19.60
GP77_SD_0_CD#19: E20.60, U$20.60
GP77_SD_0_CD#20: E21.60, U$21.60
GP77_SD_0_CD#21: E22.60, U$22.60
GP77_SD_0_CD#22: E23.60, U$23.60
GP77_SD_0_CD#23: E24.60, U$24.60
GP77_SD_0_CD#24: E25.60, U$25.60
GP77_SD_0_CD#25: E26.60, U$26.60
GP77_SD_0_CD#26: E27.60, U$27.60
GP77_SD_0_CD#27: E28.60, U$28.60
GP77_SD_0_CD#28: E29.60, U$29.60
GP77_SD_0_CD#29: E30.60, U$30.60
GP77_SD_0_CD#30: E31.60, U$31.60
GP77_SD_0_CD#31: E32.60, U$32.60
GP78: E9.26, U$9.26
GP78_SD_0_CLK: E1.58, U$3.58
GP78_SD_0_CLK1: E2.58, U$1.58
GP78_SD_0_CLK2: E3.58, U$2.58
GP78_SD_0_CLK3: E4.58, U$4.58
GP78_SD_0_CLK4: E5.58, U$5.58
GP78_SD_0_CLK5: E6.58, U$6.58
GP78_SD_0_CLK6: E7.58, U$7.58
GP78_SD_0_CLK7: E8.58, U$8.58
GP78_SD_0_CLK8: E9.58, U$9.58
GP78_SD_0_CLK9: E10.58, U$10.58
GP78_SD_0_CLK10: E11.58, U$11.58
GP78_SD_0_CLK11: E12.58, U$12.58
GP78_SD_0_CLK12: E13.58, U$13.58
GP78_SD_0_CLK13: E14.58, U$14.58
GP78_SD_0_CLK14: E15.58, U$15.58
GP78_SD_0_CLK15: E16.58, U$16.58
GP78_SD_0_CLK16: E17.58, U$17.58
GP78_SD_0_CLK17: E18.58, U$18.58
GP78_SD_0_CLK18: E19.58, U$19.58
GP78_SD_0_CLK19: E20.58, U$20.58
GP78_SD_0_CLK20: E21.58, U$21.58
GP78_SD_0_CLK21: E22.58, U$22.58
GP78_SD_0_CLK22: E23.58, U$23.58
GP78_SD_0_CLK23: E24.58, U$24.58
GP78_SD_0_CLK24: E25.58, U$25.58
GP78_SD_0_CLK25: E26.58, U$26.58
GP78_SD_0_CLK26: E27.58, U$27.58
GP78_SD_0_CLK27: E28.58, U$28.58
GP78_SD_0_CLK28: E29.58, U$29.58
GP78_SD_0_CLK29: E30.58, U$30.58
GP78_SD_0_CLK30: E31.58, U$31.58
GP78_SD_0_CLK31: E32.58, U$32.58
GP79: E9.25, U$9.25
GP79_SD_0_CMD: E1.62, U$3.62
GP79_SD_0_CMD1: E2.62, U$1.62
GP79_SD_0_CMD2: E3.62, U$2.62
GP79_SD_0_CMD3: E4.62, U$4.62
GP79_SD_0_CMD4: E5.62, U$5.62
GP79_SD_0_CMD5: E6.62, U$6.62
GP79_SD_0_CMD6: E7.62, U$7.62
GP79_SD_0_CMD7: E8.62, U$8.62
GP79_SD_0_CMD8: E9.62, U$9.62
GP79_SD_0_CMD9: E10.62, U$10.62
GP79_SD_0_CMD10: E11.62, U$11.62
GP79_SD_0_CMD11: E12.62, U$12.62
GP79_SD_0_CMD12: E13.62, U$13.62
GP79_SD_0_CMD13: E14.62, U$14.62
GP79_SD_0_CMD14: E15.62, U$15.62
GP79_SD_0_CMD15: E16.62, U$16.62
GP79_SD_0_CMD16: E17.62, U$17.62
GP79_SD_0_CMD17: E18.62, U$18.62
GP79_SD_0_CMD18: E19.62, U$19.62
GP79_SD_0_CMD19: E20.62, U$20.62
GP79_SD_0_CMD20: E21.62, U$21.62
GP79_SD_0_CMD21: E22.62, U$22.62
GP79_SD_0_CMD22: E23.62, U$23.62
GP79_SD_0_CMD23: E24.62, U$24.62
GP79_SD_0_CMD24: E25.62, U$25.62
GP79_SD_0_CMD25: E26.62, U$26.62
GP79_SD_0_CMD26: E27.62, U$27.62
GP79_SD_0_CMD27: E28.62, U$28.62
GP79_SD_0_CMD28: E29.62, U$29.62
GP79_SD_0_CMD29: E30.62, U$30.62
GP79_SD_0_CMD30: E31.62, U$31.62
GP79_SD_0_CMD31: E32.62, U$32.62
GP80: E9.24, U$9.24
GP80_SD_0_DAT0: E1.66, U$3.66
GP80_SD_0_DAT1: E2.66, U$1.66
GP80_SD_0_DAT2: E3.66, U$2.66
GP80_SD_0_DAT3: E4.66, U$4.66
GP80_SD_0_DAT4: E5.66, U$5.66
GP80_SD_0_DAT5: E6.66, U$6.66
GP80_SD_0_DAT6: E7.66, U$7.66
GP80_SD_0_DAT7: E8.66, U$8.66
GP80_SD_0_DAT8: E9.66, U$9.66
GP80_SD_0_DAT9: E10.66, U$10.66
GP80_SD_0_DAT10: E11.66, U$11.66
GP80_SD_0_DAT11: E12.66, U$12.66
GP80_SD_0_DAT12: E13.66, U$13.66
GP80_SD_0_DAT13: E14.66, U$14.66
GP80_SD_0_DAT14: E15.66, U$15.66
GP80_SD_0_DAT15: E16.66, U$16.66
GP80_SD_0_DAT16: E17.66, U$17.66
GP80_SD_0_DAT17: E18.66, U$18.66
GP80_SD_0_DAT18: E19.66, U$19.66
GP80_SD_0_DAT19: E20.66, U$20.66
GP80_SD_0_DAT20: E21.66, U$21.66
GP80_SD_0_DAT21: E22.66, U$22.66
GP80_SD_0_DAT22: E23.66, U$23.66
GP80_SD_0_DAT23: E24.66, U$24.66
GP80_SD_0_DAT24: E25.66, U$25.66
GP80_SD_0_DAT25: E26.66, U$26.66
GP80_SD_0_DAT26: E27.66, U$27.66
GP80_SD_0_DAT27: E28.66, U$28.66
GP80_SD_0_DAT28: E29.66, U$29.66
GP80_SD_0_DAT29: E30.66, U$30.66
GP80_SD_0_DAT30: E31.66, U$31.66
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
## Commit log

2014-08-08 added boards for basic console. Not ready for review yet
2014-08-12 finished layout, ready for review
2014-08-12 sch cleanup
2014-08-12 removed Edzzanine from name
2014-08-12 fixed rx tx
2014-08-14 fixed OE to high
2014-08-28 Updated Readme with small description
2014-09-24 added DCIN pin added DCIN enable circuit corrected Copper pours corrected name changed names of board and SCH replaced power button updated header footprint added units and cleaned up dimensions
2014-09-24 renamed block
2014-10-16 Rev to 10, fix gnd, pwr, txt
2014-10-17 Fix packages, silk, filter cap.
2014-10-17 Ready for reds Updated and corrected some labels on UART connector. No signal changes. No known to-do items
2014-10-22 corrected jumpers on power supply IC removed thermal relief
2014-10-22 added bottom side fids
2014-10-22 created v10 panels
2015-04-01 Updating README and directory names
